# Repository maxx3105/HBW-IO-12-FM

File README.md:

# HBW-IO-12-FM
Homematic Wired Modul mit 12 Ein- oder Ausgängen

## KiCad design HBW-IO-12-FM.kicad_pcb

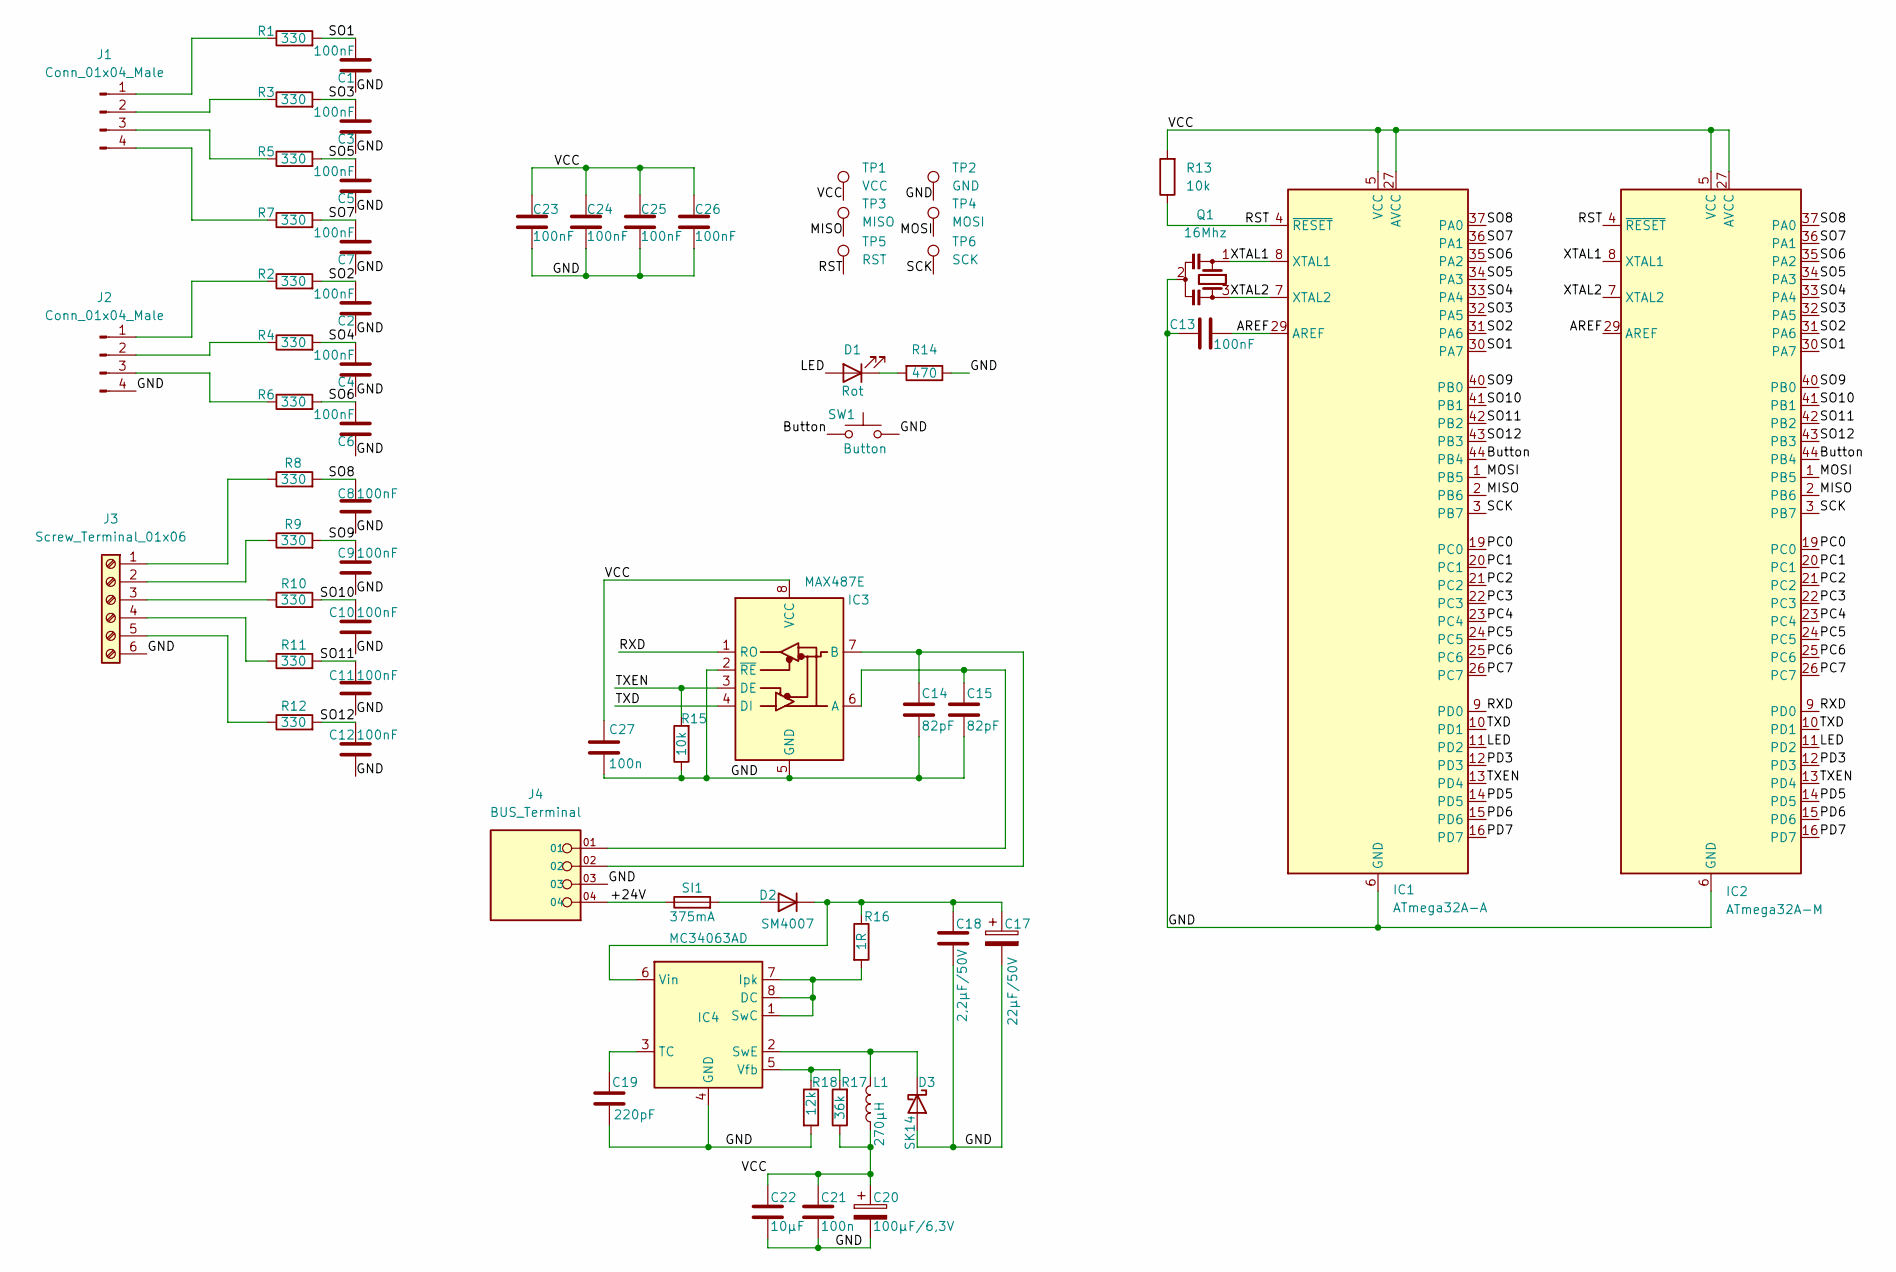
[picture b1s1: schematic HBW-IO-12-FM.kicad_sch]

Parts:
C1, C2, C3, C4, C5, C6, C7, C8, C9, C10, C11, C12, C13, C23, C24, C25, C26: 100nF; C_0805_2012Metric_Pad1.18x1.45mm_HandSolder
C14, C15: 82pF; C_0805_2012Metric_Pad1.18x1.45mm_HandSolder
C17: 22µF/50V; CP_Radial_D5.0mm_P2.50mm
C18: 2,2µF/50V; C_1210_3225Metric_Pad1.33x2.70mm_HandSolder
C19: 220pF; C_0805_2012Metric_Pad1.18x1.45mm_HandSolder
C20: 100µF/6,3V; CP_EIA-7343-20_Kemet-V_Pad2.25x2.55mm_HandSolder
C21, C27: 100n; C_0805_2012Metric_Pad1.18x1.45mm_HandSolder
C22: 10µF; C_1210_3225Metric_Pad1.33x2.70mm_HandSolder
D1: Rot; LED_0805_2012Metric_Pad1.15x1.40mm_HandSolder
D2: SM4007; D_MELF
D3: SK14; D_MELF
IC1: ATmega32A-A; TQFP-44_10x10mm_P0.8mm
IC2: ATmega32A-M; QFN-44-1EP_7x7mm_P0.5mm_EP5.2x5.2mm
IC3: MAX487E; SOIC-8_3.9x4.9mm_P1.27mm
IC4: MC34063AD; SOIC-8_3.9x4.9mm_P1.27mm
J1, J2: Conn_01x04_Male; PinHeader_1x04_P2.54mm_Vertical
J3: Screw_Terminal_01x06; TerminalBlock_MetzConnect_Type059_RT06306HBWC_1x06_P3.50mm_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
J4: BUS_Terminal; PHOENIX_1891085; PARTREV 11.03.2015
L1: 270µH; L_Taiyo-Yuden_MD-4040
Q1: 16Mhz; Resonator_SMD_Murata_CSTxExxV-3Pin_3.0x1.1mm_HandSoldering
R1, R2, R3, R4, R5, R6, R7, R8, R9, R10, R11, R12: 330; R_0805_2012Metric_Pad1.20x1.40mm_HandSolder
R13, R15: 10k; R_0805_2012Metric_Pad1.20x1.40mm_HandSolder
R14: 470; R_0805_2012Metric_Pad1.20x1.40mm_HandSolder
R16: 1R; R_0805_2012Metric_Pad1.20x1.40mm_HandSolder
R17: 36k; R_0805_2012Metric_Pad1.20x1.40mm_HandSolder
R18: 12k; R_0805_2012Metric_Pad1.20x1.40mm_HandSolder
SI1: 375mA; FUSC6127X294N
SW1: Button; SW_Push_1P1T_NO_CK_KMR2
TP1: VCC; TestPoint_Pad_D2.0mm
TP2: GND; TestPoint_Pad_D2.0mm
TP3: MISO; TestPoint_Pad_D2.0mm
TP4: MOSI; TestPoint_Pad_D2.0mm
TP5: RST; TestPoint_Pad_D2.0mm
TP6: SCK; TestPoint_Pad_D2.0mm

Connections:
/+24V: J4.04, SI1.1
/AREF: C13.2, IC1.29 (AREF), IC2.29 (AREF)
/Button: IC1.44 (PB4), IC2.44 (PB4), SW1.1
/GND: C1.1, C2.1, C3.1, C4.1, C5.1, C6.1, C7.1, C8.1, C9.1, C10.1, C11.1, C12.1, C13.1, C14.2, C15.2, C17.2, C18.2, C19.2, C20.2, C21.1, C22.2, C23.2, C24.2, C25.2, C26.2, C27.1, D3.2 (A), IC1.6 (GND), IC1.18 (GND), IC1.28 (GND), IC1.39 (GND), IC2.6 (GND), IC2.18 (GND), IC2.28 (GND), IC2.39 (GND), IC2.45 (GND), IC3.2 (~RE), IC3.5 (GND), IC4.4 (GND), J2.4, J3.6, J4.03, Q1.2, R14.1, R15.1, R18.2, SW1.2, TP2.1
/LED: D1.2 (A), IC1.11 (PD2), IC2.11 (PD2)
/MISO: IC1.2 (PB6), IC2.2 (PB6), TP3.1
/MOSI: IC1.1 (PB5), IC2.1 (PB5), TP4.1
/PC0: IC1.19 (PC0), IC2.19 (PC0)
/PC1: IC1.20 (PC1), IC2.20 (PC1)
/PC2: IC1.21 (PC2), IC2.21 (PC2)
/PC3: IC1.22 (PC3), IC2.22 (PC3)
/PC4: IC1.23 (PC4), IC2.23 (PC4)
/PC5: IC1.24 (PC5), IC2.24 (PC5)
/PC6: IC1.25 (PC6), IC2.25 (PC6)
/PC7: IC1.26 (PC7), IC2.26 (PC7)
/PD3: IC1.12 (PD3), IC2.12 (PD3)
/PD5: IC1.14 (PD5), IC2.14 (PD5)
/PD6: IC1.15 (PD6), IC2.15 (PD6)
/PD7: IC1.16 (PD7), IC2.16 (PD7)
/RST: IC1.4 (~RESET), IC2.4 (~RESET), R13.1, TP5.1
/RXD: IC1.9 (PD0), IC2.9 (PD0), IC3.1 (RO)
/SCK: IC1.3 (PB7), IC2.3 (PB7), TP6.1
/SO1: C1.2, IC1.30 (PA7), IC2.30 (PA7), R1.2
/SO2: C2.2, IC1.31 (PA6), IC2.31 (PA6), R2.2
/SO3: C3.2, IC1.32 (PA5), IC2.32 (PA5), R3.2
/SO4: C4.2, IC1.33 (PA4), IC2.33 (PA4), R4.2
/SO5: C5.2, IC1.34 (PA3), IC2.34 (PA3), R5.2
/SO6: C6.2, IC1.35 (PA2), IC2.35 (PA2), R6.2
/SO7: C7.2, IC1.36 (PA1), IC2.36 (PA1), R7.2
/SO8: C8.2, IC1.37 (PA0), IC2.37 (PA0), R8.2
/SO9: C9.2, IC1.40 (PB0), IC2.40 (PB0), R9.2
/SO10: C10.2, IC1.41 (PB1), IC2.41 (PB1), R10.2
/SO11: C11.2, IC1.42 (PB2), IC2.42 (PB2), R11.2
/SO12: C12.2, IC1.43 (PB3), IC2.43 (PB3), R12.2
/TXD: IC1.10 (PD1), IC2.10 (PD1), IC3.4 (DI)
/TXEN: IC1.13 (PD4), IC2.13 (PD4), IC3.3 (DE), R15.2
/VCC: C20.1, C21.2, C22.1, C23.1, C24.1, C25.1, C26.1, C27.2, IC1.5 (VCC), IC1.17 (VCC), IC1.27 (AVCC), IC1.38 (VCC), IC2.5 (VCC), IC2.17 (VCC), IC2.27 (AVCC), IC2.38 (VCC), IC3.8 (VCC), L1.1, R13.2, R17.1, TP1.1
/XTAL1: IC1.8 (XTAL1), IC2.8 (XTAL1), Q1.1
/XTAL2: IC1.7 (XTAL2), IC2.7 (XTAL2), Q1.3
unnamed: C14.1, IC3.7 (B), J4.02
unnamed: C15.1, IC3.6 (A), J4.01
unnamed: C17.1, C18.1, D2.1 (K), IC4.6 (Vin), R16.1
unnamed: C19.1, IC4.3 (TC)
unnamed: D1.1 (K), R14.2
unnamed: D2.2 (A), SI1.2
unnamed: D3.1 (K), IC4.2 (SwE), L1.2
unnamed: IC4.1 (SwC), IC4.7 (Ipk), IC4.8 (DC), R16.2
unnamed: IC4.5 (Vfb), R17.2, R18.1
unnamed: J1.1, R1.1
unnamed: J1.2, R3.1
unnamed: J1.3, R5.1
unnamed: J1.4, R7.1
unnamed: J2.1, R2.1
unnamed: J2.2, R4.1
unnamed: J2.3, R6.1
unnamed: J3.1, R8.1
unnamed: J3.2, R9.1
unnamed: J3.3, R10.1
unnamed: J3.4, R11.1
unnamed: J3.5, R12.1

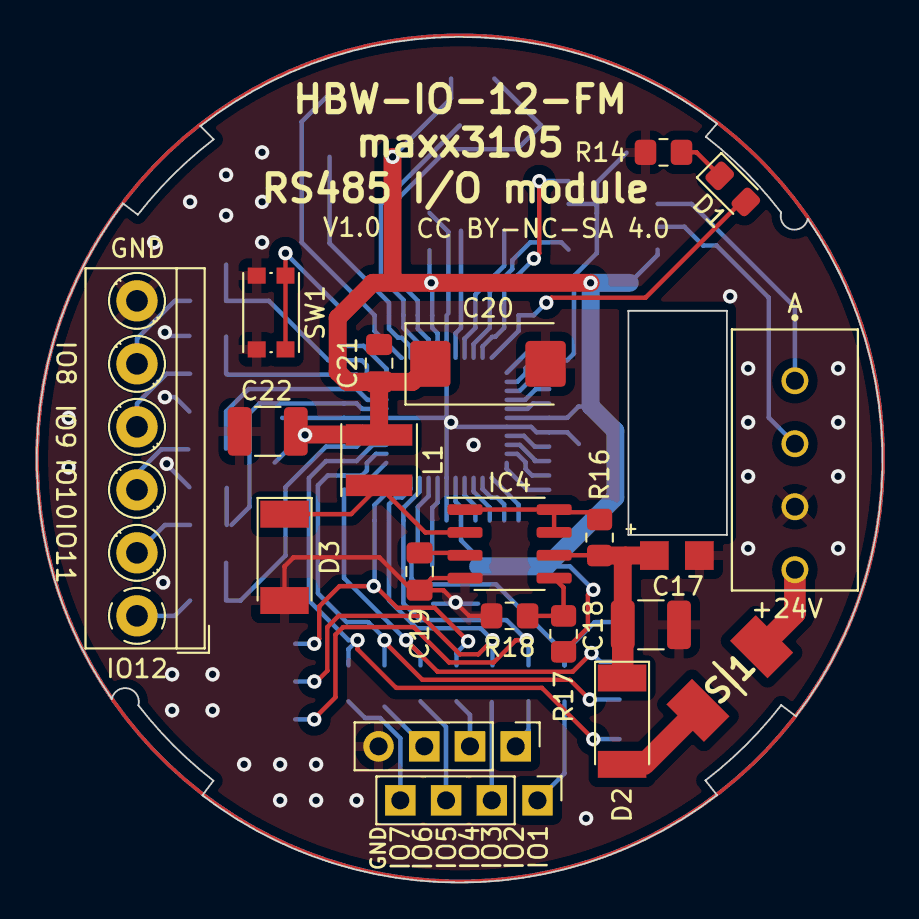
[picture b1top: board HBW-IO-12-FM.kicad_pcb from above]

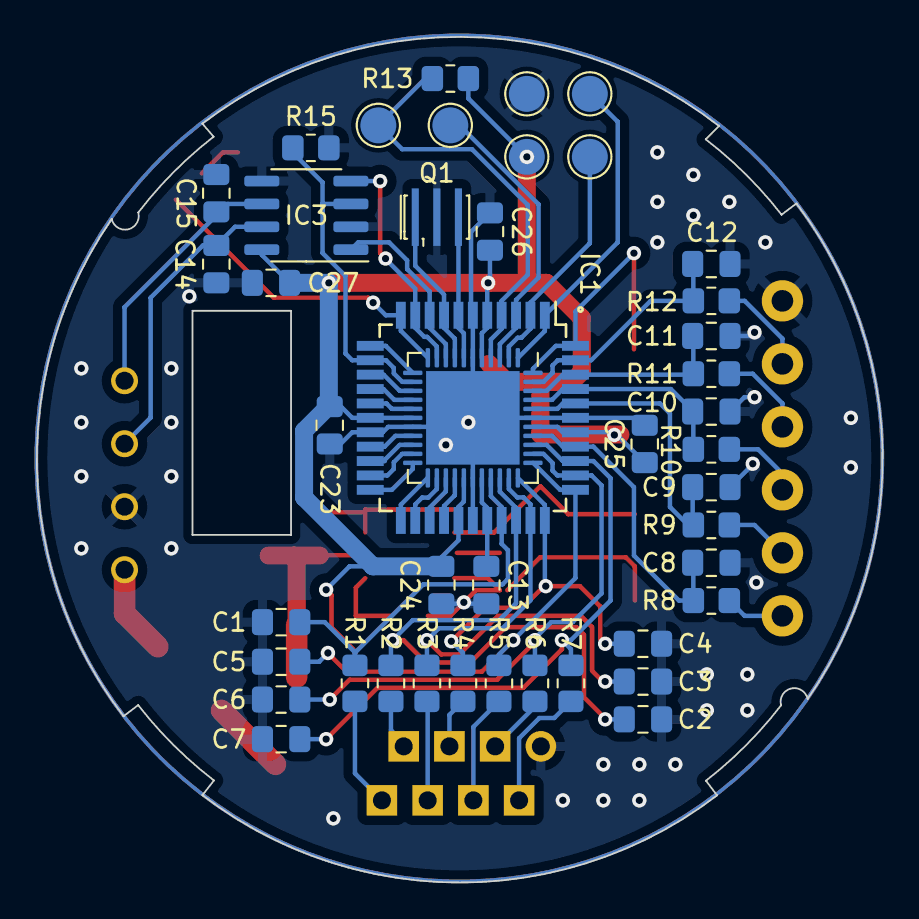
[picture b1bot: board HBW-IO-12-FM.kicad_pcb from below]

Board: 2 copper layers, 47.0 x 47.0 mm, 65 parts (44 on the bottom side), 60 nets.

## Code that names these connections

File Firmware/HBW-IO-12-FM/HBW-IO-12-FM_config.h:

/* Pin- und Hardware-Konfiguration für HBW-IO-12-FM
 *
 * Unterstützte Mikrocontroller (jeweils im Standard-Pinout der gängigen Cores):
 *   - ATmega328P     (Arduino IDE / "Arduino Nano/Uno")
 *   - ATmega32(A)    (MightyCore "Standard" pinout)        <-- HW-Ziel HBW-IO-12-FM
 *   - ATmega644P(A)  (MightyCore "Standard" pinout)
 *   - ATmega1284P    (MightyCore "Standard" pinout)
 *
 * MightyCore-Standard-Pinout (32/644/1284):
 *   PB0..PB7 = 0..7    (LED_BUILTIN = 7)
 *   PD0..PD7 = 8..15   (8=RX0, 9=TX0, 10=RX1, 11=TX1 -- nur 644P/1284P)
 *   PC0..PC7 = 16..23
 *   PA0..PA7 = 24..31  (= A0..A7)
 *
 * WICHTIG: Die Pin-Zuordnung der 12 IOs muss gegen den Schaltplan der
 * konkreten Platine geprüft werden!
 *   https://github.com/maxx3105/HBW-IO-12-FM/blob/main/HBW-IO-12-FM.pdf
 */

#ifndef HBW_IO_12_FM_CONFIG_H
#define HBW_IO_12_FM_CONFIG_H

#include <Arduino.h>
#include <EEPROM.h>
#include "FreeRam.h"

EEPROMClass* EepromPtr = &EEPROM;   // internes EEPROM

// ============================================================================
// ATmega328P  (Arduino Nano / Pro Mini / Uno -- ein UART)
// ============================================================================
#if defined(__AVR_ATmega328P__) || defined(__AVR_ATmega328__)

  // RS485 standardmäßig per SoftwareSerial, UART0 für USB-Debug.
  // Definiere USE_HARDWARE_SERIAL (z.B. via -DUSE_HARDWARE_SERIAL), um
  // RS485 auf den Hardware-UART zu legen (dann kein Debug verfügbar).

  #define IO1   A3
  #define IO2   10
  #define IO3   11
  #define IO4   A0
  #define IO5   A1
  #define IO6   A2
  #define IO7   A4
  #define IO8   A5
  #define IO9    9
  #define IO10   7
  #define IO11   6
  #define IO12   5

  #define LED   LED_BUILTIN     // D13

  #ifdef USE_HARDWARE_SERIAL
    #define RS485_TXEN  2
    #define BUTTON      A6
    #define HBW_RS485       (Serial)
    #define HBW_DEBUGSTREAM (NULL)
    #define HBW_BEGIN_SERIALS() do { Serial.begin(19200, SERIAL_8E1); } while (0)
  #else
    #define RS485_RXD   4
    #define RS485_TXD   2
    #define RS485_TXEN  3
    #define BUTTON      8

    #include <HBWSoftwareSerial.h>
    HBWSoftwareSerial rs485(RS485_RXD, RS485_TXD);
    #define HBW_RS485       (rs485)
    #define HBW_DEBUGSTREAM (&Serial)
    #define HBW_BEGIN_SERIALS() do { Serial.begin(115200); rs485.begin(19200); } while (0)
  #endif

// ============================================================================
// ATmega32 / ATmega32A  (MightyCore -- ein UART, kein Serial1)
// ============================================================================
#elif defined(__AVR_ATmega32__) || defined(__AVR_ATmega32A__)

  // 12 IOs: PA7..PA0 (31..24) + PB0..PB3 (0..3)  -- an die Hardware angepasst
  #define IO1   31    // PA7
  #define IO2   30    // PA6
  #define IO3   29    // PA5
  #define IO4   28    // PA4
  #define IO5   27    // PA3
  #define IO6   26    // PA2
  #define IO7   25    // PA1
  #define IO8   24    // PA0
  #define IO9   0     // PB0
  #define IO10  1     // PB1
  #define IO11  2     // PB2
  #define IO12  3     // PB3

  #define LED   10    // PD2 
  #define BUTTON      4       // PB4
  // -- RS485 auf Hardware-UART:  RO -> Pin 8 (PD0/RX0),  DI -> Pin 9 (PD1/TX0) --
  #define RS485_TXEN  12        // PD4  -> Transceiver DE (+ /RE zusammen)
  #define HBW_RS485       (Serial)
  #define HBW_DEBUGSTREAM (NULL)
  #define HBW_BEGIN_SERIALS() do { Serial.begin(19200, SERIAL_8E1); } while (0)


// ============================================================================
// ATmega644P(A) / ATmega1284P  (MightyCore -- pinkompatibel zum 32A)
// ============================================================================
#elif defined(__AVR_ATmega644P__)  || defined(__AVR_ATmega644PA__) \
   || defined(__AVR_ATmega1284P__) || defined(__AVR_ATmega1284__)

  // Pinkompatibel zum 32A (selbe Platine) -> identische Belegung.
  // RS485 deshalb auch hier auf dem ERSTEN UART (Serial/PD0/PD1), NICHT Serial1:
  // dessen RX1 ist PD2, und PD2 ist die LED. -> kein Geraete-Debug (UART = Bus,
  // wie 32A). Vorteil 644P/1284P: groesseres EEPROM (Adresse weit ueber den
  // Links, keine 30-Input-Link-Ueberlapp-Frage wie auf dem 1KB-32A).
  // 12 IOs: PA7..PA0 (31..24) + PB0..PB3 (0..3)
  #define IO1   31    // PA7
  #define IO2   30    // PA6
  #define IO3   29    // PA5
  #define IO4   28    // PA4
  #define IO5   27    // PA3
  #define IO6   26    // PA2
  #define IO7   25    // PA1
  #define IO8   24    // PA0
  #define IO9   0     // PB0
  #define IO10  1     // PB1
  #define IO11  2     // PB2
  #define IO12  3     // PB3

  #define LED          10       // PD2
  #define BUTTON       4        // PB4
  #define RS485_TXEN   12       // PD4  -> Transceiver DE (+ /RE zusammen)
  #define HBW_RS485       (Serial)        // RS485 auf UART0 (PD0/RX0, PD1/TX0), wie 32A
  #define HBW_DEBUGSTREAM (NULL)
  #define HBW_BEGIN_SERIALS() do { Serial.begin(19200, SERIAL_8E1); } while (0)

#else
  #error "HBW-IO-12-FM: Nicht unterstuetzter Mikrocontroller. Erlaubt: ATmega328P, ATmega32(A), ATmega644P(A), ATmega1284P."
#endif

#endif  // HBW_IO_12_FM_CONFIG_H

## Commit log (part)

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2024-03-13 Add files via upload
    Bigger hole for tht capacitor.
2024-03-26 Add button for firmware reset.
2026-06-23 Refactor pin definitions for LED and BUTTON
2026-06-24 Refactor IO pin definitions and RS485 settings

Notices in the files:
HBW-IO-12-FM.kicad_pcb:
CC BY-NC-SA 4.0
